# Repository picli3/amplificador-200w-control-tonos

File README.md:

# amplificador-200w-control-tonos

Diseño de amplificador de audio con control de tonos, pensado para integrar etapa de potencia y acondicionamiento de señal en una sola solución de hardware.

## Qué incluye
- esquemáticos o archivos de diseño en KiCad
- PCB o documentación asociada
- base reutilizable para análisis, fabricación o mejora del proyecto

## Propósito general
Este repositorio busca concentrar el diseño de hardware del proyecto en un formato editable y reutilizable, facilitando pruebas, documentación y futuras iteraciones del circuito.

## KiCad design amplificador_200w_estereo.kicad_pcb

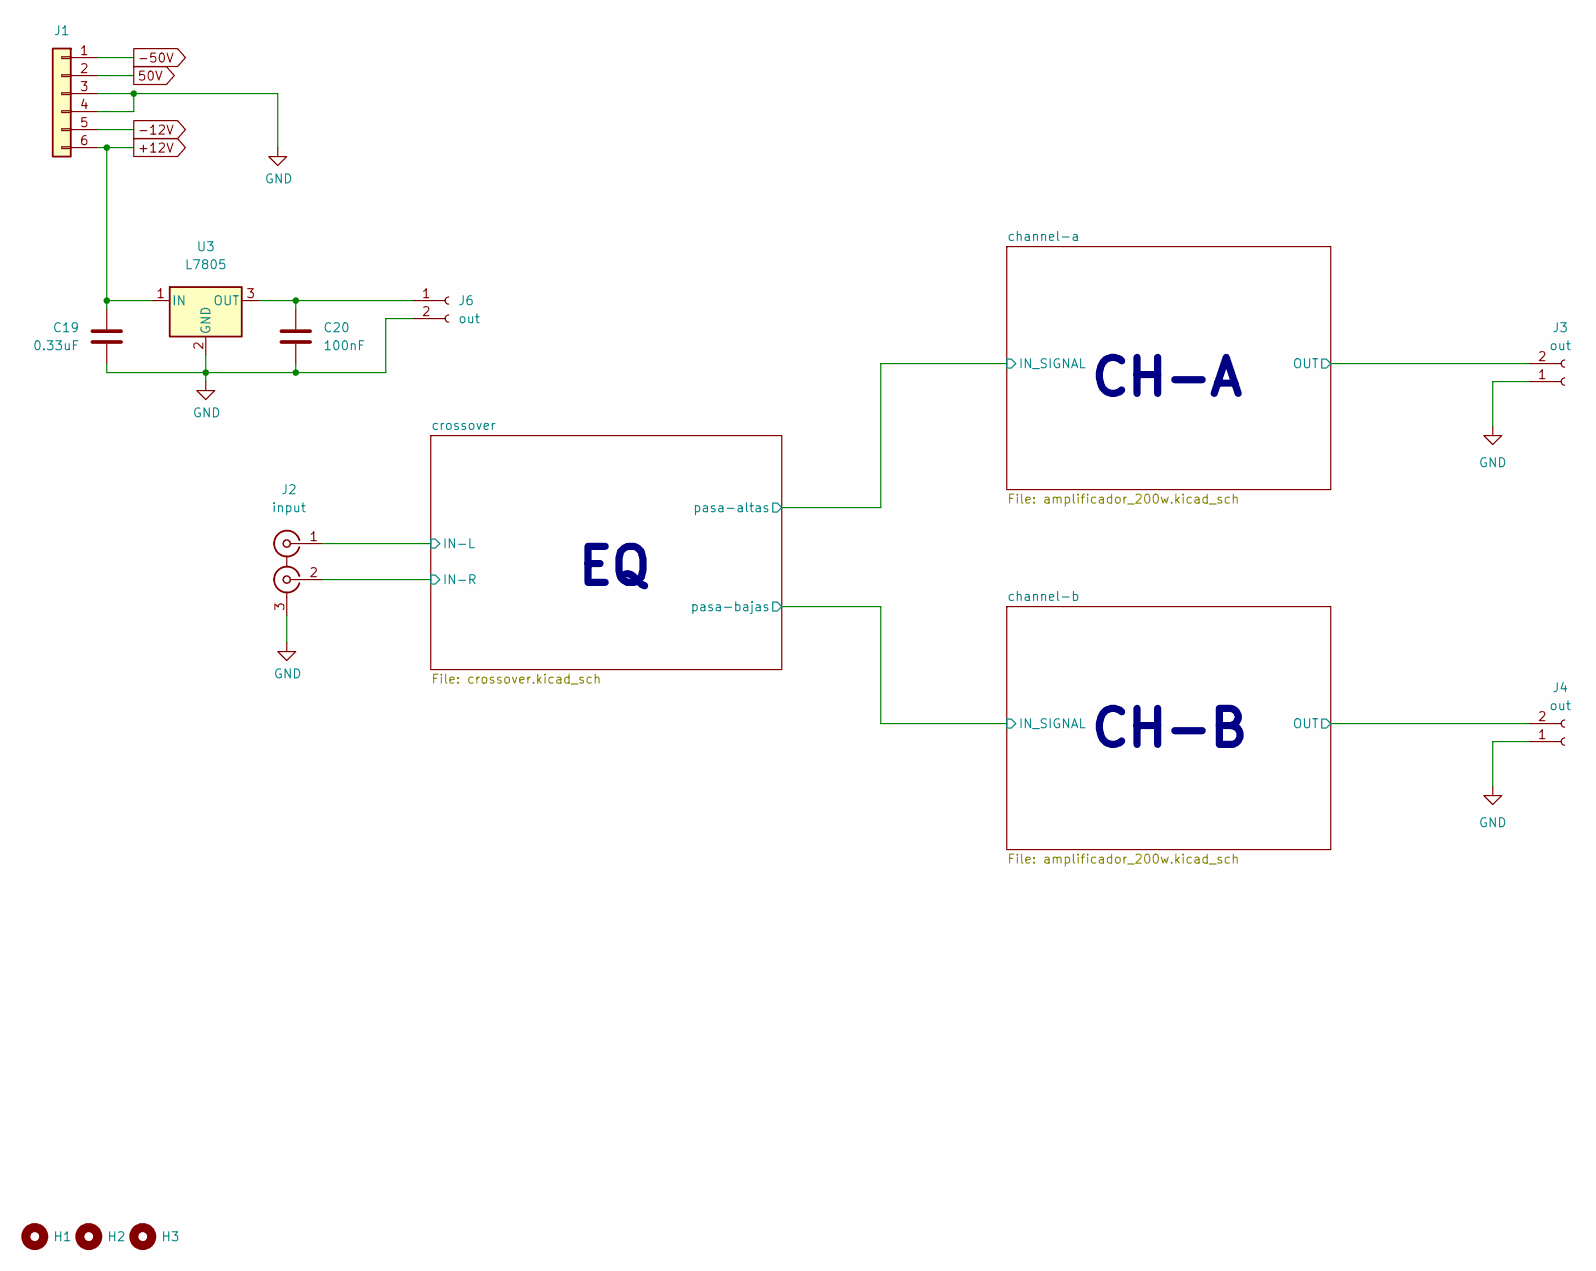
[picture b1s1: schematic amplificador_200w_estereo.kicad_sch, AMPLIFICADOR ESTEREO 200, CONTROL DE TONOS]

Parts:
C19: 0.33uF; C_Disc_D5.0mm_W2.5mm_P5.00mm
C20: 100nF; C_Disc_D5.0mm_W2.5mm_P5.00mm
H1, H2, H3: MountingHole; MountingHole_3.2mm_M3_ISO14580_Pad
J1: Conn_01x03; TerminalBlock_Phoenix_MKDS-1,5-6-5.08_1x06_P5.08mm_Horizont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
J2: input; CUI_RCJ-21XX
J3, J4, J6: out; TerminalBlock_Phoenix_MKDS-1,5-2-5.08_1x02_P5.08mm_Horizont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
U3: L7805; TO-220-3_Vertical

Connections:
50V: J1.2; also elsewhere on the board
+12V: C19.1, J1.6, U3.1 (IN); also elsewhere on the board
-12V: J1.5; also elsewhere on the board
-50V: J1.1; also elsewhere on the board
/channel-b/OUT: J4.2; also elsewhere on the board
GND: C19.2, C20.2, J1.3, J1.4, J2.3 (EXT), J3.1, J4.1, J6.2, U3.2 (GND); also elsewhere on the board
unnamed 34: C20.1, J6.1, U3.3 (OUT); also elsewhere on the board

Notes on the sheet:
CH-B
CH-A

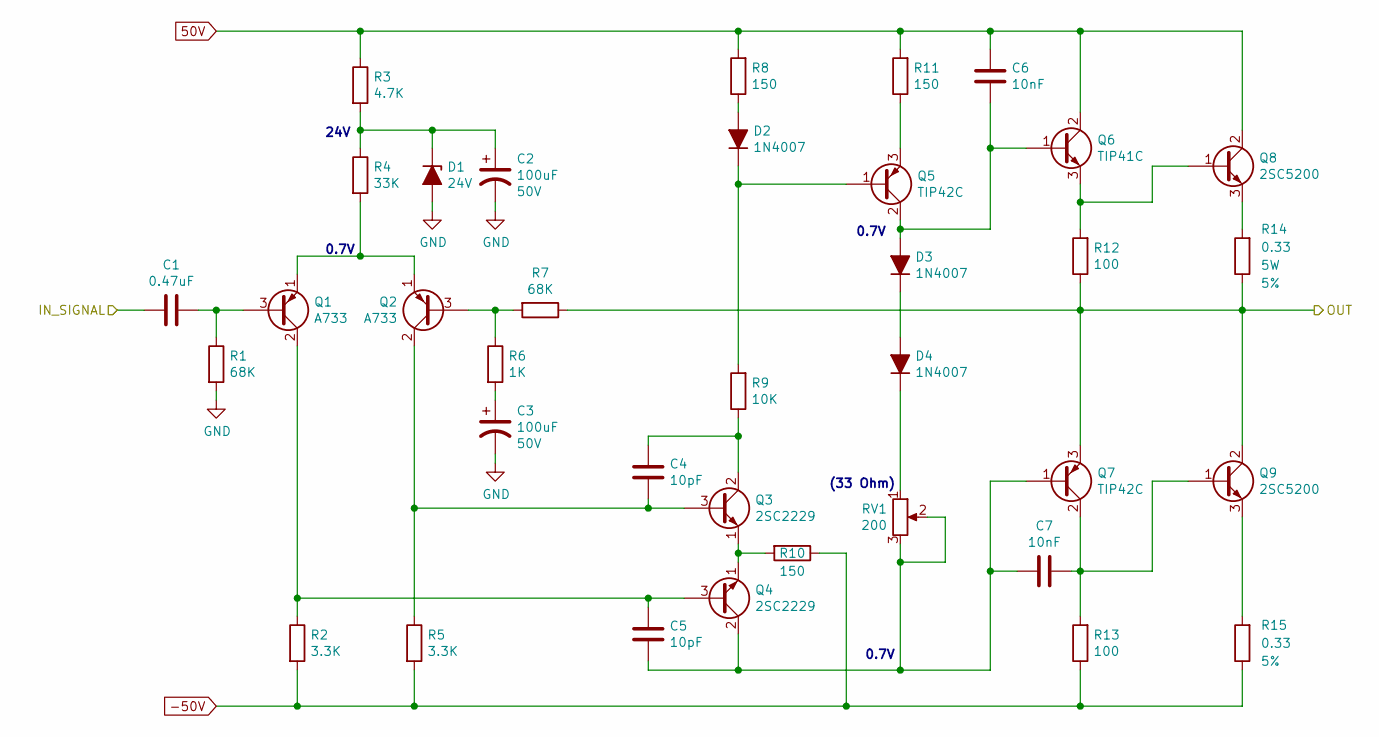
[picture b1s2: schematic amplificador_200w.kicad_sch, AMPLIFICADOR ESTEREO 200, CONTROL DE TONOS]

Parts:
C1: 0.47uF; C_Disc_D9.0mm_W2.5mm_P5.00mm
C2, C3: 100uF; CP_Radial_D8.0mm_P3.50mm
C4, C5: 10pF; C_Disc_D5.0mm_W2.5mm_P5.00mm
C6, C7: 10nF; C_Disc_D9.0mm_W2.5mm_P5.00mm
D1: 24V; D_A-405_P10.16mm_Horizontal
D2, D3, D4: 1N4007; D_DO-41_SOD81_P10.16mm_Horizontal
Q1, Q2: A733; TO-92L_HandSolder; Mfg Part # KSA733CGBU
Q3, Q4: 2SC2229; TO-92L_HandSolder
Q5, Q7: TIP42C; TO-220-3_Vertical
Q6: TIP41C; TO-220-3_Vertical
Q8, Q9: 2SC5200; TO-264-3_Vertical
R1, R7: 68K; R_Axial_DIN0207_L6.3mm_D2.5mm_P10.16mm_Horizontal
R2, R5: 3.3K; R_Axial_DIN0207_L6.3mm_D2.5mm_P10.16mm_Horizontal
R3: 4.7K; R_Axial_DIN0207_L6.3mm_D2.5mm_P10.16mm_Horizontal
R4: 33K; R_Axial_DIN0207_L6.3mm_D2.5mm_P10.16mm_Horizontal
R6: 1K; R_Axial_DIN0207_L6.3mm_D2.5mm_P10.16mm_Horizontal
R8, R10, R11: 150; R_Axial_DIN0207_L6.3mm_D2.5mm_P10.16mm_Horizontal
R9: 10K; R_Axial_DIN0207_L6.3mm_D2.5mm_P10.16mm_Horizontal
R12, R13: 100; R_Axial_DIN0516_L15.5mm_D5.0mm_P20.32mm_Horizontal
R14, R15: 0.33; R_Axial_Power_L25.0mm_W9.0mm_P10.16mm_Vertical
RV1: 200; Potentiometer_Runtron_RM-065_Vertical

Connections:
50V: C6.2, Q6.2 (C), Q8.2 (C), R3.1, R8.2, R11.2; also elsewhere on the board
-50V: R2.2, R5.2, R10.1, R13.1, R15.1; also elsewhere on the board
/channel-a/IN_SIGNAL: C1.2; also elsewhere on the board
/channel-a/OUT: Q7.3 (E), Q9.2 (C), R7.1, R12.1, R14.1; also elsewhere on the board
GND: C2.2, C3.2, D1.2 (A), R1.2; also elsewhere on the board
unnamed: C1.1, Q1.3 (B), R1.1
unnamed: C2.1, D1.1 (K), R3.2, R4.1
unnamed: C3.1, R6.2
unnamed: C4.1, Q2.2 (C), Q3.3 (B), R5.1
unnamed: C4.2, Q3.2 (C), R9.1
unnamed: C5.1, C7.1, Q4.2 (C), Q7.1 (B), RV1.2, RV1.3
unnamed: C5.2, Q1.2 (C), Q4.3 (B), R2.1
unnamed: C6.1, D3.2 (A), Q5.2 (C), Q6.1 (B)
unnamed: C7.2, Q7.2 (C), Q9.1 (B), R13.2
unnamed: D2.1 (K), Q5.1 (B), R9.2
unnamed: D2.2 (A), R8.1
unnamed: D3.1 (K), D4.2 (A)
unnamed: D4.1 (K), RV1.1
unnamed: Q1.1 (E), Q2.1 (E), R4.2
unnamed: Q2.3 (B), R6.1, R7.2
unnamed: Q3.1 (E), Q4.1 (E), R10.2
unnamed: Q5.3 (E), R11.1
unnamed: Q6.3 (E), Q8.1 (B), R12.2
unnamed: Q8.3 (E), R14.2
unnamed: Q9.3 (E), R15.2

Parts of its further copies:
C8: 0.47uF; C_Disc_D9.0mm_W2.5mm_P5.00mm
C9, C10: 100uF; CP_Radial_D8.0mm_P3.50mm
C11, C12: 10pF; C_Disc_D5.0mm_W2.5mm_P5.00mm
C13, C14: 10nF; C_Disc_D9.0mm_W2.5mm_P5.00mm
D5: 24V; D_A-405_P10.16mm_Horizontal
D6, D7, D8: 1N4007; D_DO-41_SOD81_P10.16mm_Horizontal
Q10, Q11: A733; TO-92L_HandSolder; Mfg Part # KSA733CGBU
Q12, Q13: 2SC2229; TO-92L_HandSolder
Q14, Q16: TIP42C; TO-220-3_Vertical
Q15: TIP41C; TO-220-3_Vertical
Q17, Q18: 2SC5200; TO-264-3_Vertical
R16, R22: 68K; R_Axial_DIN0207_L6.3mm_D2.5mm_P10.16mm_Horizontal
R17, R20: 3.3K; R_Axial_DIN0207_L6.3mm_D2.5mm_P10.16mm_Horizontal
R18: 4.7K; R_Axial_DIN0207_L6.3mm_D2.5mm_P10.16mm_Horizontal
R19: 33K; R_Axial_DIN0207_L6.3mm_D2.5mm_P10.16mm_Horizontal
R21: 1K; R_Axial_DIN0207_L6.3mm_D2.5mm_P10.16mm_Horizontal
R23, R25, R26: 150; R_Axial_DIN0207_L6.3mm_D2.5mm_P10.16mm_Horizontal
R24: 10K; R_Axial_DIN0207_L6.3mm_D2.5mm_P10.16mm_Horizontal
R27, R28: 100; R_Axial_DIN0516_L15.5mm_D5.0mm_P20.32mm_Horizontal
R29, R30: 0.33; R_Axial_Power_L25.0mm_W9.0mm_P10.16mm_Vertical
RV2: 200; Potentiometer_Runtron_RM-065_Vertical

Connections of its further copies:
50V: C13.2, Q15.2 (C), Q17.2 (C), R18.1, R23.2, R26.2; also elsewhere on the board
-50V: R17.2, R20.2, R25.1, R28.1, R30.1; also elsewhere on the board
/channel-b/IN_SIGNAL: C8.2; also elsewhere on the board
/channel-b/OUT: Q16.3 (E), Q18.2 (C), R22.1, R27.1, R29.1; also elsewhere on the board
GND: C9.2, C10.2, D5.2 (A), R16.2; also elsewhere on the board
unnamed: C8.1, Q10.3 (B), R16.1
unnamed: C9.1, D5.1 (K), R18.2, R19.1
unnamed: C10.1, R21.2
unnamed: C11.1, Q11.2 (C), Q12.3 (B), R20.1
unnamed: C11.2, Q12.2 (C), R24.1
unnamed: C12.1, C14.1, Q13.2 (C), Q16.1 (B), RV2.2, RV2.3
unnamed: C12.2, Q10.2 (C), Q13.3 (B), R17.1
unnamed: C13.1, D7.2 (A), Q14.2 (C), Q15.1 (B)
unnamed: C14.2, Q16.2 (C), Q18.1 (B), R28.2
unnamed: D6.1 (K), Q14.1 (B), R24.2
unnamed: D6.2 (A), R23.1
unnamed: D7.1 (K), D8.2 (A)
unnamed: D8.1 (K), RV2.1
unnamed: Q10.1 (E), Q11.1 (E), R19.2
unnamed: Q11.3 (B), R21.1, R22.2
unnamed: Q12.1 (E), Q13.1 (E), R25.2
unnamed: Q14.3 (E), R26.1
unnamed: Q15.3 (E), Q17.1 (B), R27.2
unnamed: Q17.3 (E), R29.2
unnamed: Q18.3 (E), R30.2

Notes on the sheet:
0.7V
(33 Ohm)
24V

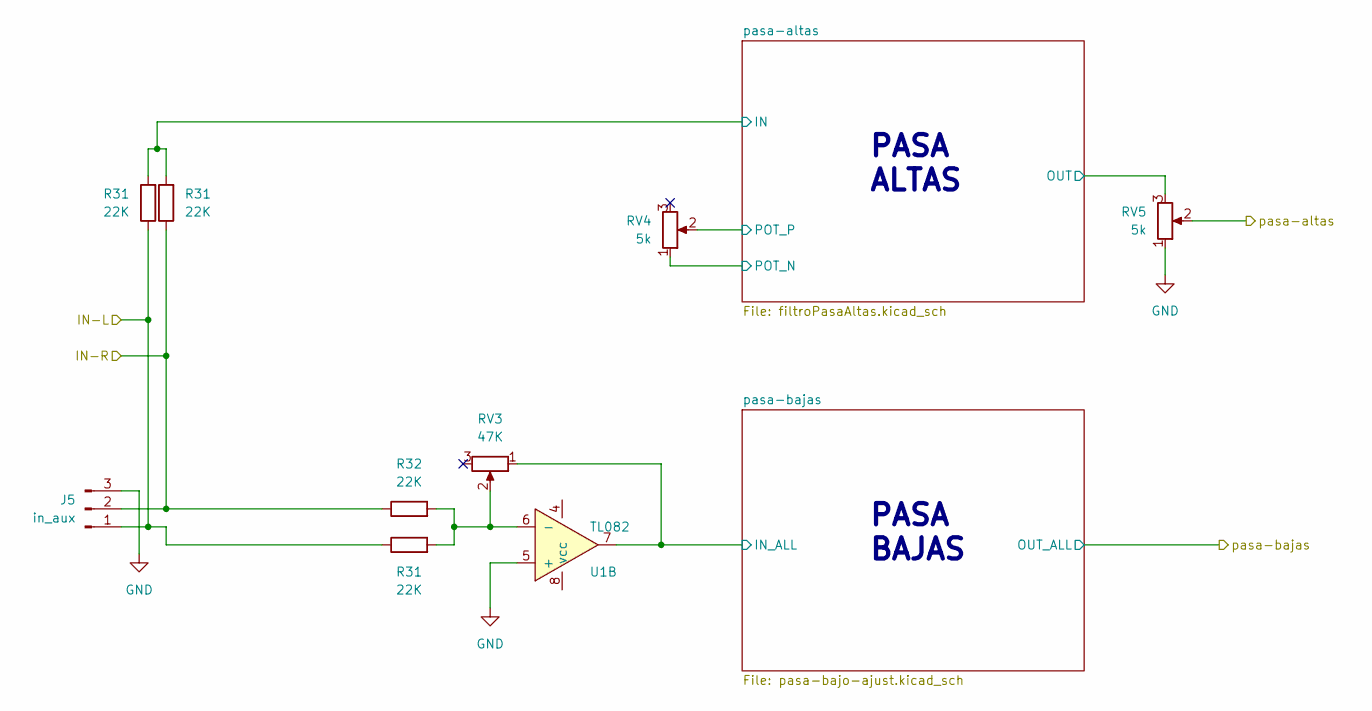
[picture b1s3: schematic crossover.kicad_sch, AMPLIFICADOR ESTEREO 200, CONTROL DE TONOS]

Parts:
J5: in_aux; PinSocket_1x03_P2.54mm_Vertical
R31, R32: 22K; R_Axial_DIN0207_L6.3mm_D2.5mm_P10.16mm_Horizontal
RV3: 47K; Potentiometer_Alps_RK163_Single_Horizontal
RV4, RV5: 5k; Potentiometer_Alps_RK163_Single_Horizontal
U1: TL082; DIP-8_W7.62mm_LongPads

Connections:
+12V: U1.8 (vcc); also elsewhere on the board
-12V: U1.4; also elsewhere on the board
/channel-a/IN_SIGNAL: RV5.2; also elsewhere on the board
/crossover/pasa-altas/OUT: RV5.3; also elsewhere on the board
/crossover/pasa-altas/POT_N: RV4.1; also elsewhere on the board
/crossover/pasa-altas/POT_P: RV4.2; also elsewhere on the board
/crossover/pasa-bajas/IN_ALL: RV3.1, U1.7; also elsewhere on the board
GND: J5.3, RV5.1, U1.5 (+); also elsewhere on the board

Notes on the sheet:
PASA ALTAS
PASA BAJAS

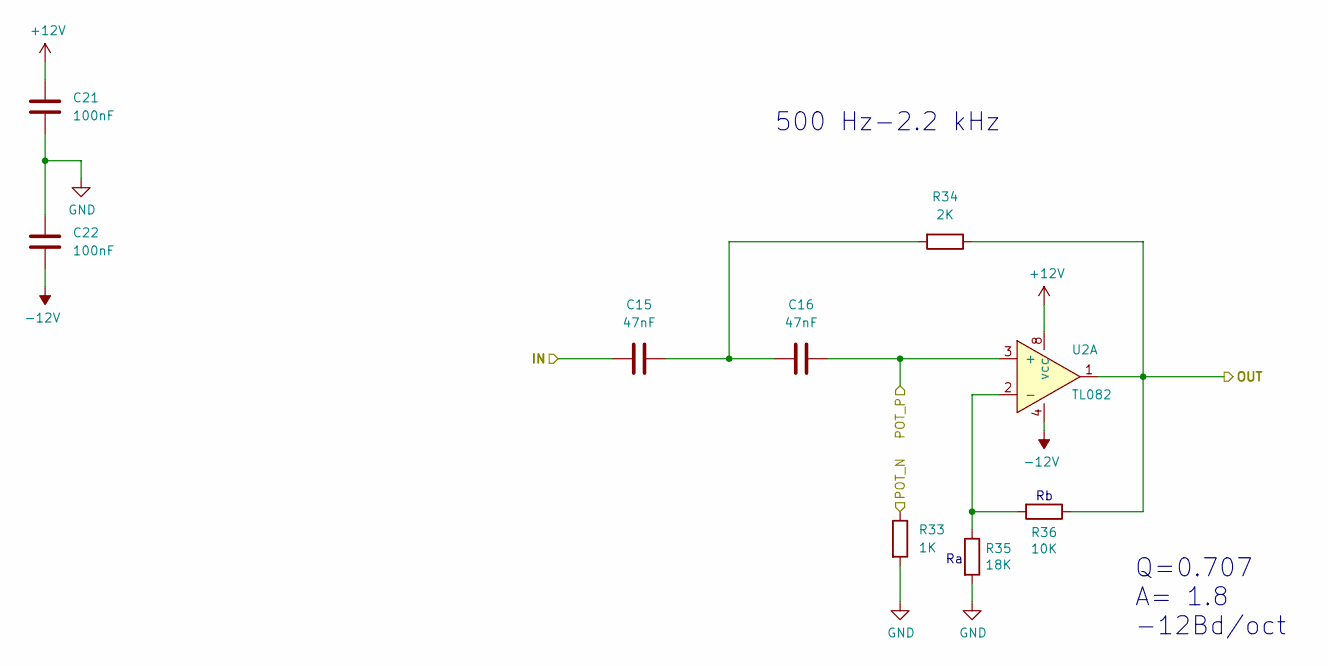
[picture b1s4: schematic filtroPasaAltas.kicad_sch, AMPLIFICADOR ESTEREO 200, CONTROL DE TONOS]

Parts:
C15, C16: 47nF; C_Disc_D4.3mm_W1.9mm_P5.00mm
C21, C22: 100nF; C_Disc_D5.0mm_W2.5mm_P5.00mm
R33: 1K; R_Axial_DIN0207_L6.3mm_D2.5mm_P10.16mm_Horizontal
R34: 2K; R_Axial_DIN0207_L6.3mm_D2.5mm_P10.16mm_Horizontal
R35: 18K; R_Axial_DIN0207_L6.3mm_D2.5mm_P10.16mm_Horizontal
R36: 10K; R_Axial_DIN0207_L6.3mm_D2.5mm_P10.16mm_Horizontal
U2: TL082; DIP-8_W7.62mm_LongPads

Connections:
+12V: C21.1, U2.8 (vcc); also elsewhere on the board
-12V: C22.2, U2.4; also elsewhere on the board
/crossover/pasa-altas/OUT: R34.1, R36.1, U2.1; also elsewhere on the board
/crossover/pasa-altas/POT_N: R33.1; also elsewhere on the board
/crossover/pasa-altas/POT_P: C16.1, U2.3 (+); also elsewhere on the board
GND: C21.2, C22.1, R33.2, R35.2; also elsewhere on the board
unnamed: C15.1, C16.2, R34.2
unnamed: R35.1, R36.2, U2.2 (-)

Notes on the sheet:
Q=0.707 A= 1.8 -12Bd/oct
500 Hz-2.2 kHz

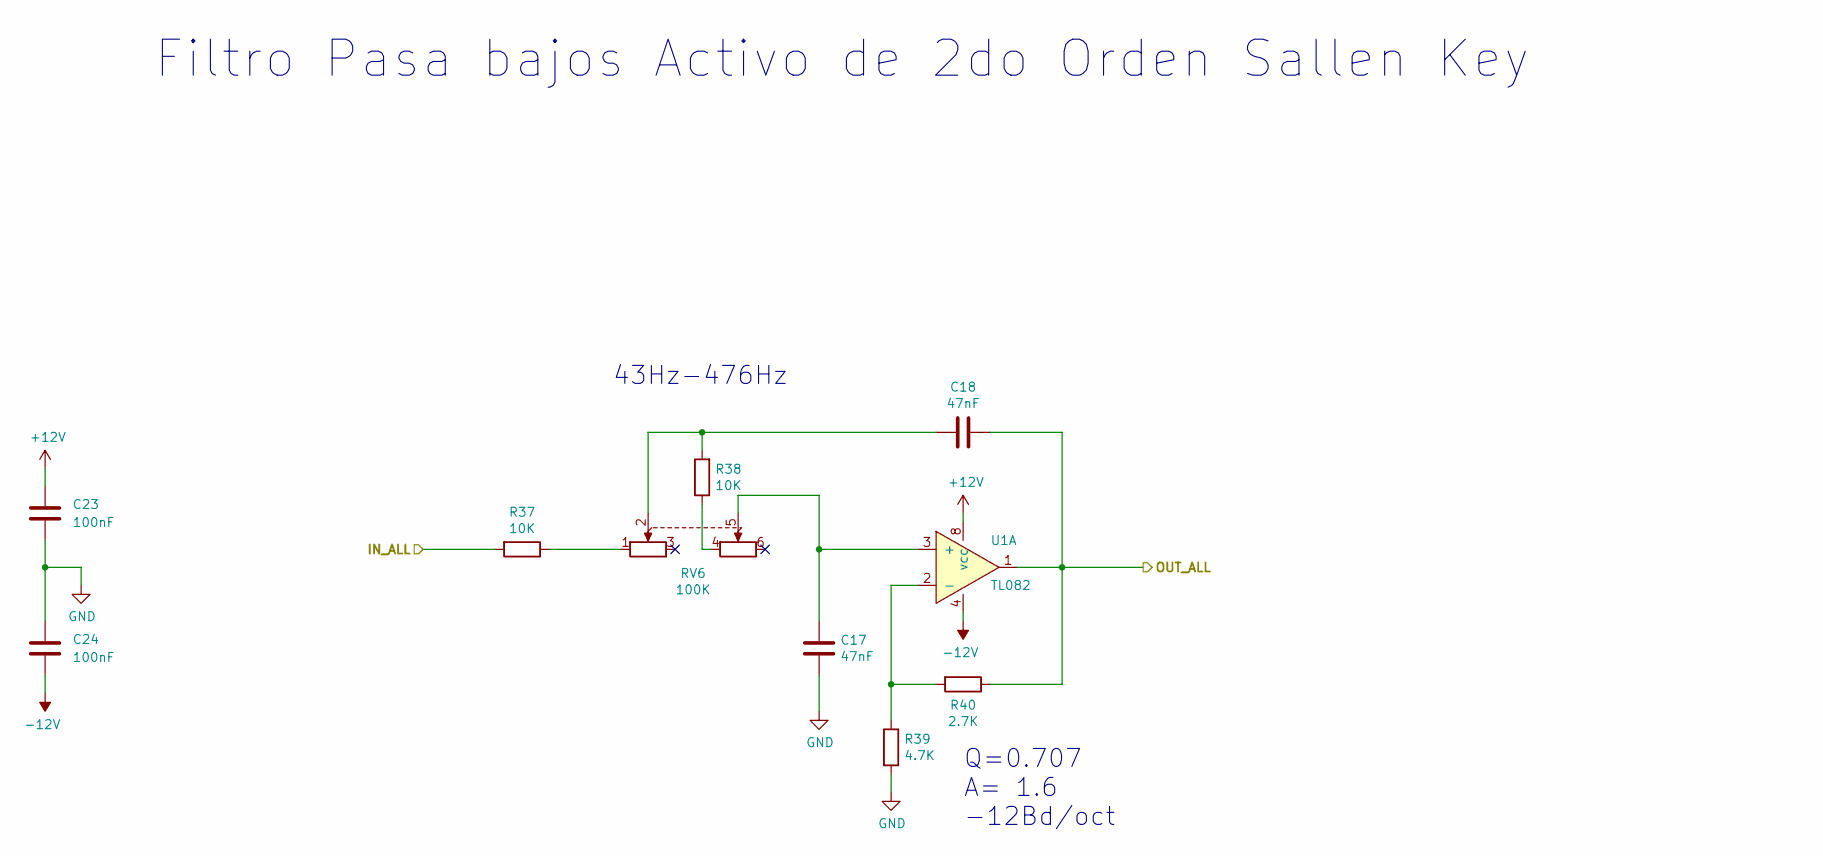
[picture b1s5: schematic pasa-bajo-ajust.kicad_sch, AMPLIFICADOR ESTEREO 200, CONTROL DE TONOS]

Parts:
C17, C18: 47nF; C_Disc_D4.3mm_W1.9mm_P5.00mm
C23, C24: 100nF; C_Disc_D5.0mm_W2.5mm_P5.00mm
R37, R38: 10K; R_Axial_DIN0207_L6.3mm_D2.5mm_P10.16mm_Horizontal
R39: 4.7K; R_Axial_DIN0207_L6.3mm_D2.5mm_P10.16mm_Horizontal
R40: 2.7K; R_Axial_DIN0207_L6.3mm_D2.5mm_P10.16mm_Horizontal
RV6: 100K; Potentiometer_Alps_RK163_Dual_Horizontal
U1: TL082; DIP-8_W7.62mm_LongPads

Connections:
+12V: C23.1, U1.8 (vcc); also elsewhere on the board
-12V: C24.2, U1.4; also elsewhere on the board
/channel-b/IN_SIGNAL: C18.1, R40.1, U1.1; also elsewhere on the board
/crossover/pasa-bajas/IN_ALL: R37.2; also elsewhere on the board
GND: C17.1, C23.2, C24.1, R39.2; also elsewhere on the board
unnamed: C17.2, RV6.5, U1.3 (+)
unnamed: C18.2, R38.2, RV6.2
unnamed: R37.1, RV6.1
unnamed: R38.1, RV6.4
unnamed: R39.1, R40.2, U1.2 (-)

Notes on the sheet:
Filtro Pasa bajos Activo de 2do Orden Sallen Key
Q=0.707 A= 1.6 -12Bd/oct
43Hz-476Hz

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
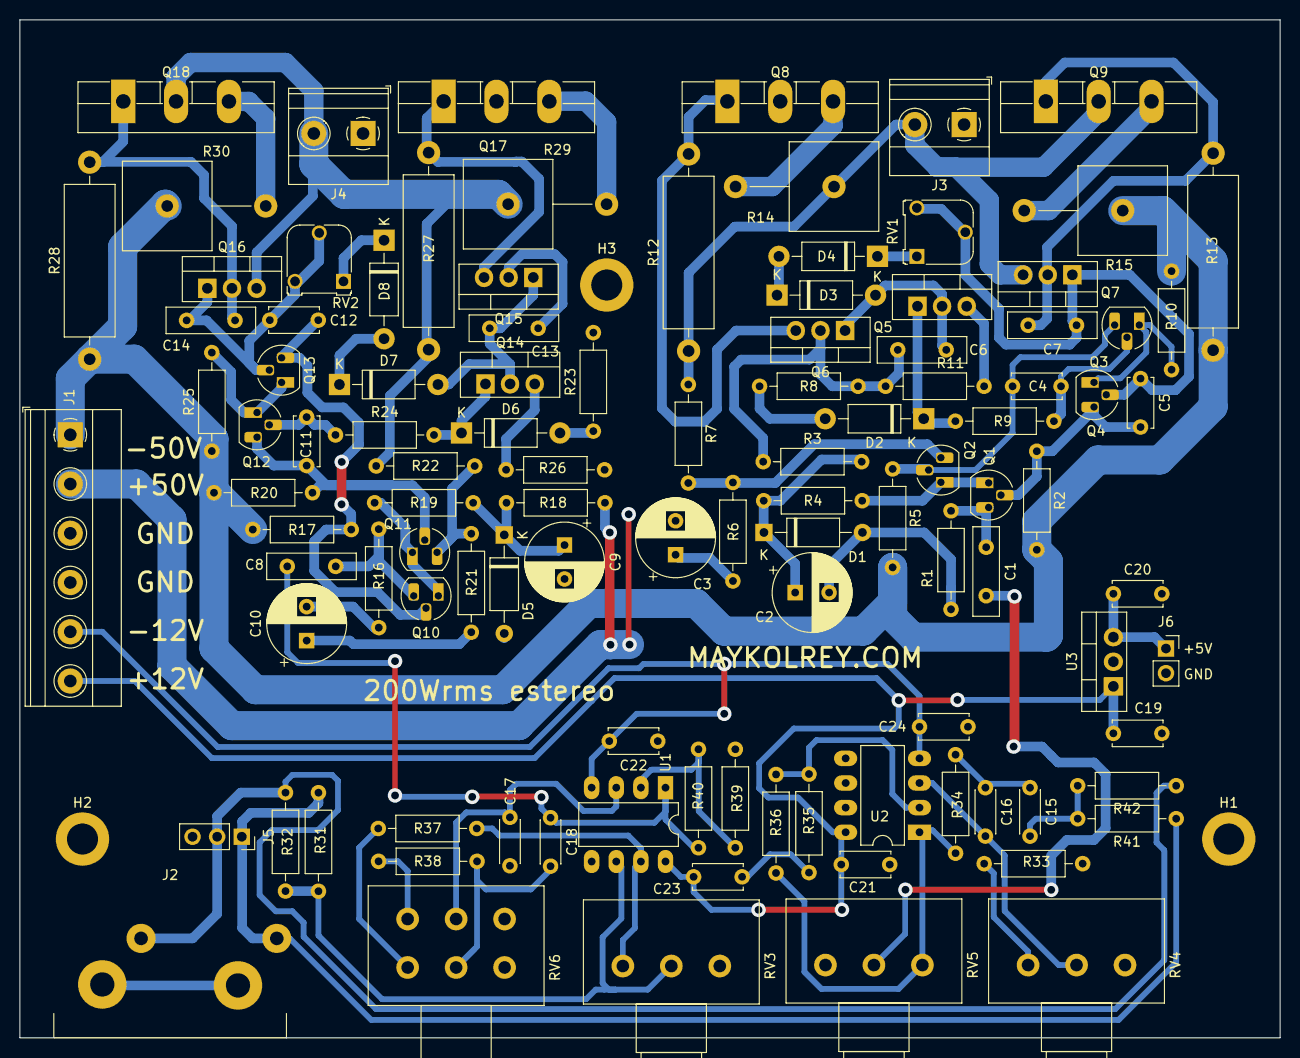
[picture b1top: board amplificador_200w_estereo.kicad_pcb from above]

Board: 2 copper layers, 130.0 x 105.0 mm, 110 parts (0 on the bottom side), 65 nets.

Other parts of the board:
J?: out; PinSocket_1x02_P2.54mm_Vertical
J?#2: out; TerminalBlock_Phoenix_MKDS-1,5-2-5.08_1x02_P5.08mm_Horizont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
R31#2, R31#3: 22K; R_Axial_DIN0207_L6.3mm_D2.5mm_P10.16mm_Horizontal

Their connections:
/channel-a/OUT: J?#2.2; also elsewhere on the board
GND: J?.2, J?#2.1; also elsewhere on the board
unnamed 34: J?.1; also elsewhere on the board

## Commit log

2021-12-12 primera fabricacion
2022-01-07 Separando las altas con resistencias de 22K
2023-03-07 actualizando a kicad 7
2023-03-11 agregando archivos pdf del pcb
2026-04-29 Agrega README con descripción inicial del proyecto
